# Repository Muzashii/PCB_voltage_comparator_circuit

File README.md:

# PCB_voltage_comparator_circuit

PBC of a voltage comparator circuit done on a college assignment

# Imagens

Schematic of the project (1/2): 

Schematic of the project (2/2): 

Schematic of the PCB : 

Top layer of 3D PCB : 

## Installation

##### Use KiCad to open the project file

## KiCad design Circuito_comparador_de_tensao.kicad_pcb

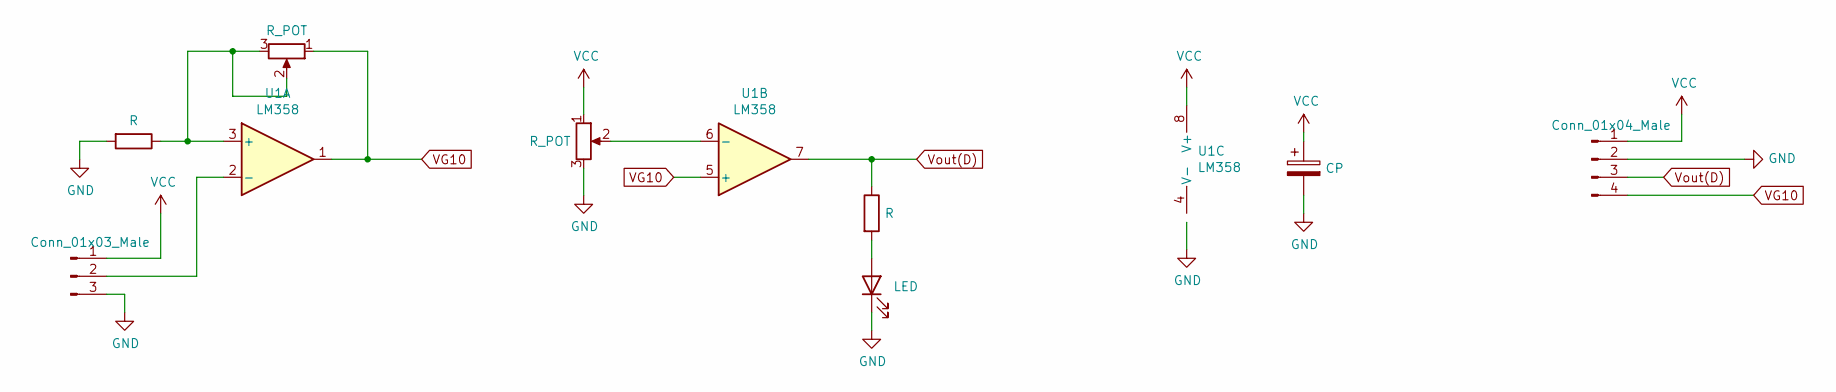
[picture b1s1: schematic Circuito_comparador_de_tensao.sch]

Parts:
C1: CP; CP_Radial_D8.0mm_P3.50mm
D1: LED; LED_D5.0mm
J1: Conn_01x03_Male; PinHeader_1x03_P2.54mm_Vertical
J2: Conn_01x04_Male; PinHeader_1x04_P2.54mm_Vertical
R1, R2: R; R_Axial_DIN0207_L6.3mm_D2.5mm_P10.16mm_Horizontal
RV1, RV2: R_POT; Potentiometer_Bourns_3296W_Vertical
U1: LM358; DIP-8_W7.62mm_LongPads

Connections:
GND: C1.2, D1.1 (K), J1.3, J2.2, R1.2, RV2.3
unnamed: D1.2 (A), R2.2
unnamed: J1.2, U1.2 (-)
unnamed: R1.1, RV1.2, RV1.3, U1.3 (+)
unnamed: RV2.2, U1.6 (-)
VCC: C1.1, J1.1, J2.1, RV2.1, U1.8 (V+)
VG10: J2.4, RV1.1, U1.1, U1.5 (+)
Vout(D): J2.3, R2.1, U1.7

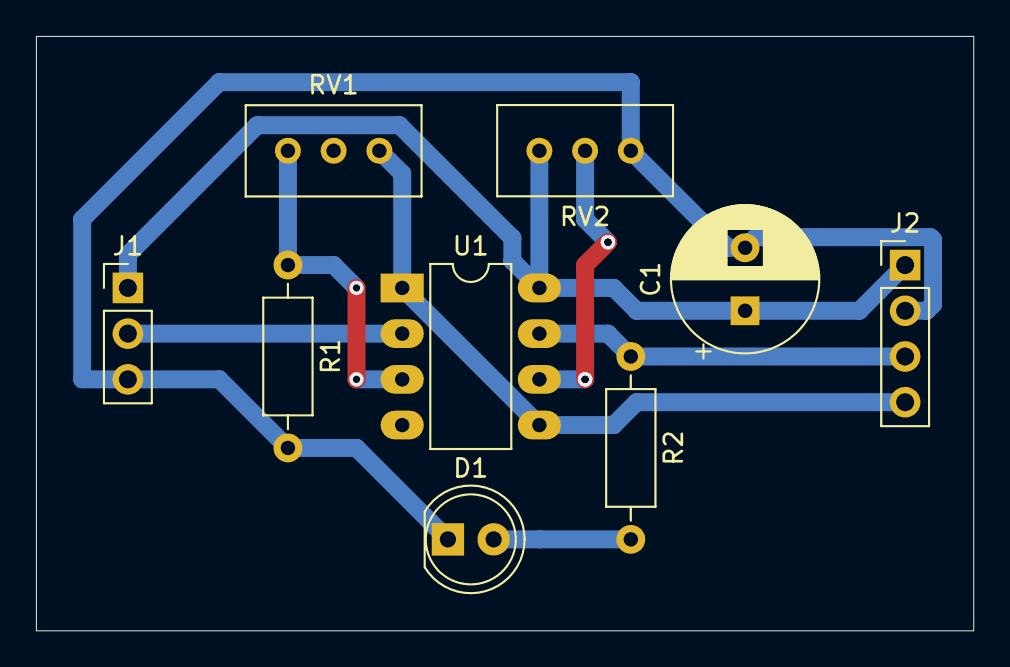
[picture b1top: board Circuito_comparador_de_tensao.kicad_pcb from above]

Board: 2 copper layers, 52.1 x 33.0 mm, 9 parts (0 on the bottom side), 8 nets.

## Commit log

2021-05-31 finished project
2021-05-31 PCB Final
